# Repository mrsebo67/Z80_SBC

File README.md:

# Z80_SBC
Z80 single board computer

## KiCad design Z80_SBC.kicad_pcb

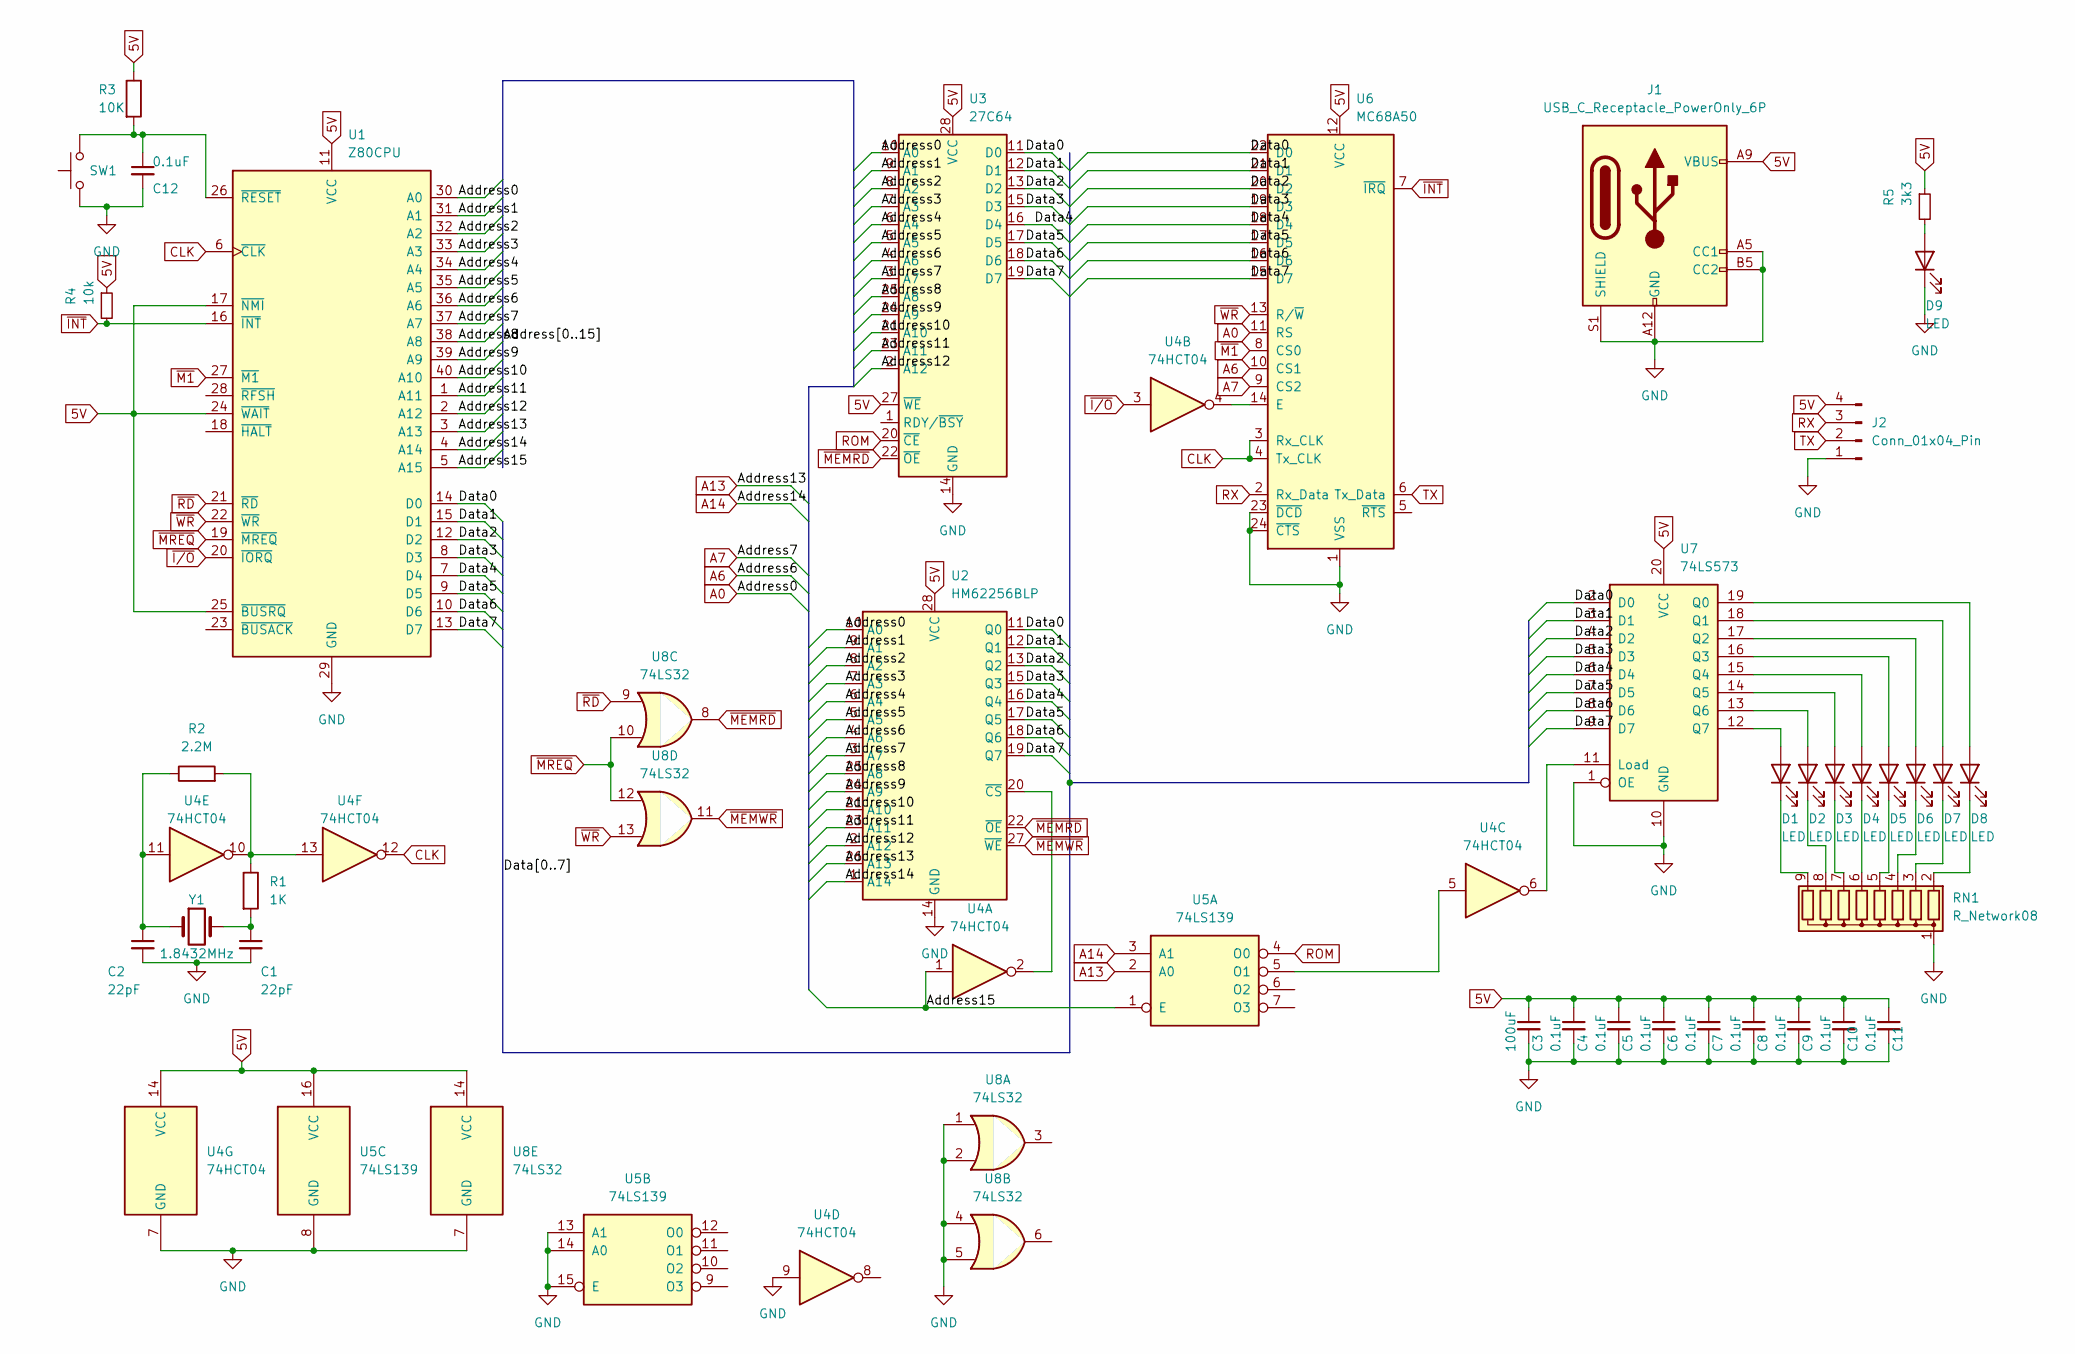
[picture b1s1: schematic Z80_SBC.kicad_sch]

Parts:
C1, C2: 22pF; CP_Radial_D4.0mm_P2.00mm
C3: 100uF; CP_Radial_D4.0mm_P1.50mm
C4, C5, C6, C7, C8, C9, C10, C11, C12: 0.1uF; C_Radial_D4.0mm_H5.0mm_P1.50mm
D1, D2, D3, D4, D5, D6, D7, D8, D9: LED; LED_D3.0mm
J1: USB_C_Receptacle_PowerOnly_6P; USB_C_Receptacle_GCT_USB4125-xx-x_6P_TopMnt_Horizontal
J2: Conn_01x04_Pin; PinHeader_1x04_P1.27mm_Vertical
R1: 1K; R_Axial_DIN0309_L9.0mm_D3.2mm_P12.70mm_Horizontal
R2: 2.2M; R_Axial_DIN0309_L9.0mm_D3.2mm_P12.70mm_Horizontal
R3: 10K; R_Axial_DIN0309_L9.0mm_D3.2mm_P12.70mm_Horizontal
R4: 10k; R_Axial_DIN0309_L9.0mm_D3.2mm_P12.70mm_Horizontal
R5: 3k3; R_Axial_DIN0309_L9.0mm_D3.2mm_P12.70mm_Horizontal
RN1: R_Network08; R_Array_SIP9
SW1: SW_Push; SW_PUSH_6mm
U1: Z80CPU; DIP-40_W15.24mm_LongPads
U2: HM62256BLP; DIP-28_W15.24mm
U3: 27C64; DIP-28_W15.24mm_LongPads
U4: 74HCT04; DIP-14_W7.62mm
U5: 74LS139; DIP-16_W7.62mm
U6: MC68A50; DIP-24_W15.24mm
U7: 74LS573; DIP-20_W7.62mm
U8: 74LS32; DIP-14_W7.62mm
Y1: 1.8432MHz; Crystal_HC18-U_Vertical

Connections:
5V: C3.1, C4.1, C5.1, C6.1, C7.1, C8.1, C9.1, C10.1, C11.1, J1.A9 (VBUS), J1.B9 (VBUS), J2.4, R3.1, R4.1, R5.1, U1.11 (VCC), U1.17 (~NMI), U1.24 (~WAIT), U1.25 (~BUSRQ), U2.28 (VCC), U3.27 (~WE), U3.28 (VCC), U4.14 (VCC), U5.16 (VCC), U6.12 (VCC), U7.20 (VCC), U8.14 (VCC)
/Address1: U1.31 (A1), U2.9 (A1), U3.9 (A1)
/Address2: U1.32 (A2), U2.8 (A2), U3.8 (A2)
/Address3: U1.33 (A3), U2.7 (A3), U3.7 (A3)
/Address4: U1.34 (A4), U2.6 (A4), U3.6 (A4)
/Address5: U1.35 (A5), U2.5 (A5), U3.5 (A5)
/Address8: U1.38 (A8), U2.25 (A8), U3.25 (A8)
/Address9: U1.39 (A9), U2.24 (A9), U3.24 (A9)
/Address10: U1.40 (A10), U2.21 (A10), U3.21 (A10)
/Address11: U1.1 (A11), U2.23 (A11), U3.23 (A11)
/Address12: U1.2 (A12), U2.2 (A12), U3.2 (A12)
/Address15: U1.5 (A15), U4.1, U5.1 (E)
/Data0: U1.14 (D0), U2.11 (Q0), U3.11 (D0), U6.22 (D0), U7.2 (D0)
/Data1: U1.15 (D1), U2.12 (Q1), U3.12 (D1), U6.21 (D1), U7.3 (D1)
/Data2: U1.12 (D2), U2.13 (Q2), U3.13 (D2), U6.20 (D2), U7.4 (D2)
/Data3: U1.8 (D3), U2.15 (Q3), U3.15 (D3), U6.19 (D3), U7.5 (D3)
/Data4: U1.7 (D4), U2.16 (Q4), U3.16 (D4), U6.18 (D4), U7.6 (D4)
/Data5: U1.9 (D5), U2.17 (Q5), U3.17 (D5), U6.17 (D5), U7.7 (D5)
/Data6: U1.10 (D6), U2.18 (Q6), U3.18 (D6), U6.16 (D6), U7.8 (D6)
/Data7: U1.13 (D7), U2.19 (Q7), U3.19 (D7), U6.15 (D7), U7.9 (D7)
A0: U1.30 (A0), U2.10 (A0), U3.10 (A0), U6.11 (RS)
A6: U1.36 (A6), U2.4 (A6), U3.4 (A6), U6.10 (CS1)
A7: U1.37 (A7), U2.3 (A7), U3.3 (A7), U6.9 (CS2)
A13: U1.3 (A13), U2.26 (A13), U5.2 (A0)
A14: U1.4 (A14), U2.1 (A14), U5.3 (A1)
CLK: U1.6 (~CLK), U4.12, U6.3 (Rx_CLK), U6.4 (Tx_CLK)
GND: C1.2, C2.2, C3.2, C4.2, C5.2, C6.2, C7.2, C8.2, C9.2, C10.2, C11.2, C12.2, D9.1 (K), J1.A5 (CC1), J1.A12 (GND), J1.B5 (CC2), J1.B12 (GND), J1.S1 (SHIELD), J2.1, RN1.1 (common), SW1.1, U1.29 (GND), U2.14 (GND), U3.14 (GND), U4.7 (GND), U4.9, U5.8 (GND), U5.13 (A1), U5.14 (A0), U5.15 (E), U6.1 (VSS), U6.23 (~DCD), U6.24 (~CTS), U7.1 (OE), U7.10 (GND), U8.1, U8.2, U8.4, U8.5, U8.7 (GND)
unnamed: C1.1, R1.2, Y1.2
unnamed: C2.1, R2.1, U4.11, Y1.1
unnamed: D1.2 (A), U7.12 (Q7)
unnamed: D1.1 (K), RN1.9 (R8)
unnamed: D2.2 (A), U7.13 (Q6)
unnamed: D2.1 (K), RN1.8 (R7)
unnamed: D3.2 (A), U7.14 (Q5)
unnamed: D3.1 (K), RN1.7 (R6)
unnamed: D4.2 (A), U7.15 (Q4)
unnamed: D4.1 (K), RN1.6 (R5)
unnamed: D5.2 (A), U7.16 (Q3)
unnamed: D5.1 (K), RN1.5 (R4)
unnamed: D6.2 (A), U7.17 (Q2)
unnamed: D6.1 (K), RN1.4 (R3)
unnamed: D7.2 (A), U7.18 (Q1)
unnamed: D7.1 (K), RN1.3 (R2)
unnamed: D8.2 (A), U7.19 (Q0)
unnamed: D8.1 (K), RN1.2 (R1)
unnamed: D9.2 (A), R5.2
unnamed: R1.1, R2.2, U4.10, U4.13
unnamed: C12.1, R3.2, SW1.2, U1.26 (~RESET)
unnamed: U2.20 (~CS), U4.2
unnamed: U4.5, U5.5 (O1)
unnamed: U4.4, U6.14 (E)
unnamed: U4.6, U7.11 (Load)
ROM: U3.20 (~CE), U5.4 (O0)
RX: J2.3, U6.2 (Rx_Data)
TX: J2.2, U6.6 (Tx_Data)
~INT: R4.2, U1.16 (~INT), U6.7 (~IRQ)
~I/O: U1.20 (~IORQ), U4.3
~M1: U1.27 (~M1), U6.8 (CS0)
~MEMRD: U2.22 (~OE), U3.22 (~OE), U8.8
~MEMWR: U2.27 (~WE), U8.11
~MREQ: U1.19 (~MREQ), U8.10, U8.12
~RD: U1.21 (~RD), U8.9
~WR: U1.22 (~WR), U6.13 (R/~W), U8.13

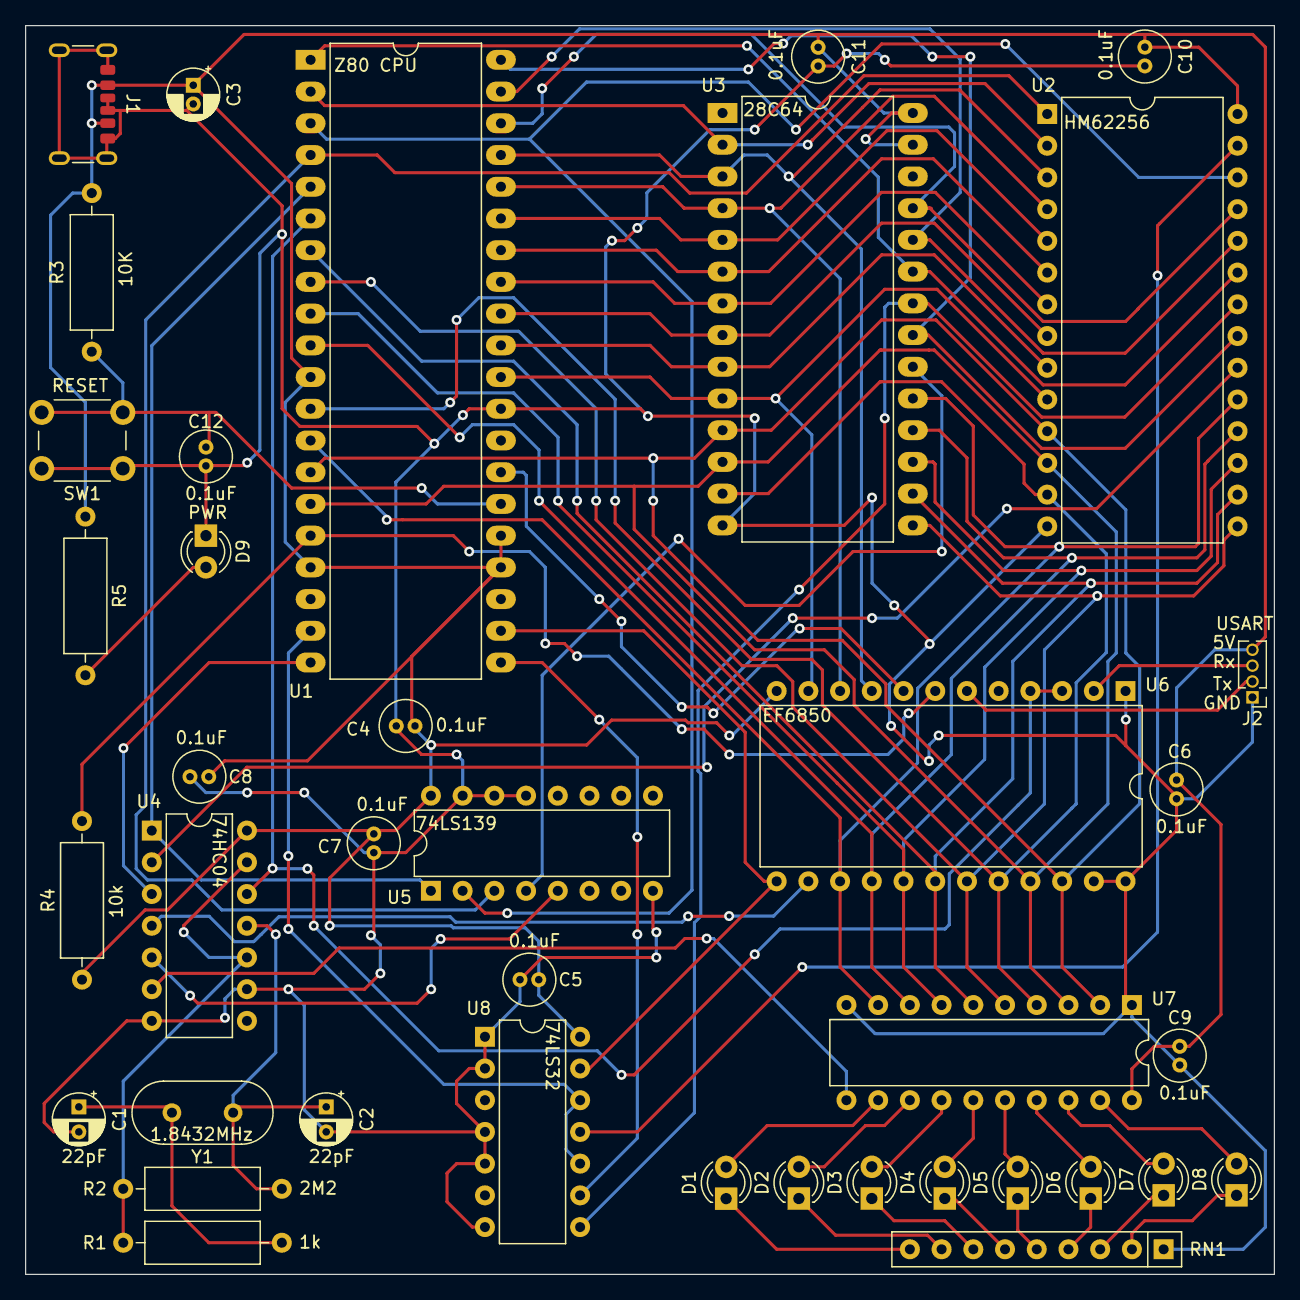
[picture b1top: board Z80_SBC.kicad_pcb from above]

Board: 2 copper layers, 100.0 x 100.0 mm, 39 parts (0 on the bottom side), 63 nets.

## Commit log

2023-10-07 add basics
2023-10-07 Create README.md
    Add readme
2023-10-07 add license
2023-10-08 added 6850 USART
2023-10-09 poor route
2023-10-09 fix DRC errors and warning, add reset and power
2023-10-09 organise dir
2023-10-09 minor fixes
2023-10-09 update images
2023-10-09 add route image
